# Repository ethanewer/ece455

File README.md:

# ECE 455 proton magnetometer

One proton precession magnetometer design: a polarization board, a signal-processing and control board with a Raspberry Pi Pico 2 and an ADS1256 ADC, an off-board two-stage amplifier, the sensing and polarizing coils, and the Pico firmware. [`docs/design.md`](docs/design.md) describes how they fit together and lists open issues.

## Layout

Design files, one folder per type:

| Folder | Contents | Edit with |
|---|---|---|
| [`kicad/`](kicad/) | Polarization board and signal-processing & control board: schematics, PCBs, Gerbers, BOM | KiCad 10 |
| [`ltspice/`](ltspice/) | `AmplificationSim.asc`: coil, tuning tank, and the off-board amplifier | LTspice |
| [`firmware/`](firmware/) | Pico 2 ADS1256 capture and frequency firmware, and its serial plotter | Pico SDK 2.3.1 |
| [`spreadsheets/`](spreadsheets/) | `CoilDesign.xlsx`: coil windings and polarizing field; `TuningCapacitors.xlsx`: measured coil inductances and LC tuning | Excel |
| [`3d_models/`](3d_models/) | Sensing coil V1 and polarizing coil V2 forms: SolidWorks parts and sliced print files | SolidWorks, Bambu Studio |

Everything else:

- [`util/`](util/) reads those files and holds the simulation, breadboard layout, firmware host harness, and tests.
- [`docs/`](docs/) has the design description, the verification plan, generated simulation and breadboard reports, datasheets, and references.
- `local/` is for uncommitted output.

## Setup

```sh
python3 -m venv .venv
. .venv/bin/activate
pip install -e '.[test,bench]'
brew install ngspice        # or: sudo apt-get install ngspice
```

`make firmware` and `make test` compile the firmware on the host with `$CC`, or clang or gcc. Building and flashing the Pico needs the Pico SDK and Arm toolchain; see [`firmware/README.md`](firmware/README.md).

## Commands

```sh
make test         # all tests: board/schematic/BOM/firmware consistency, coil forms, LTspice translation, breadboard, estimator
make firmware     # only the firmware estimator tests
make sim          # simulate ltspice/AmplificationSim.asc and regenerate docs/simulation/
make breadboard   # check the breadboard layout and regenerate docs/breadboard/
make verify       # test, sim, and breadboard
make flash        # build the Pico firmware and flash it over USB
make plot         # plot captures from the Pico (sets up .venv on first use)
```

## Status

Both PCBs match their schematics, and the firmware's SPI pins match the ADS1256 header on J3. The amplifier exists only as an LTspice drawing and a breadboard layout; no op amp has been chosen. From the coil workbook and print files, the coils as built should give a best-case FID of about 2 µV, a fifth of the drawing's 10 µV. The coil forms are sized for the sensing coils to sit inside the polarizing coil, where its turn-off would induce on the order of 100 V in them, beyond what the damping switch and amplifier input are rated for. The firmware now polarizes and captures on a button press but does not drive the damping switch. Nothing here has been measured on hardware; see [`docs/verification-plan.md`](docs/verification-plan.md).

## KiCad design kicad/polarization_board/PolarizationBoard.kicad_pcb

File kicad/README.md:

# KiCad projects

Two KiCad 10 projects. Open the `.kicad_pro` file in KiCad.

| Folder | Board | Files |
|---|---|---|
| `polarization_board/` | Battery, fuse, 12 V regulator, TC4420 gate driver, and the NMOS switch and TVS for the polarizing coil | `PolarizationBoard.kicad_{pro,sch,pcb}`, `gerbers/` |
| `signal_control_board/` | Coil input, switched tuning bank, damping switch, amplifier connectors J5/J6, 5 V buck converter, 2.5 V bias, ADC input network, sockets for the ADS1256 module, and the Pico 2 | `SignalProcessing&ControlBoard.kicad_{pro,sch,pcb}`, sub-sheets `SignalProcessing.kicad_sch` and `MCU.kicad_sch`, `gerbers/`, and the BOM export `SignalProcessing&ControlBoard.csv` |

Keep the file names: the root schematic refers to its sub-sheets by name. After changing a board, re-export its Gerbers into `gerbers/` (and the signal board's BOM CSV), then run `make test`. The tests read these files directly with `util/kicad.py`. They check each board's nets against its schematic and compare the boards with the firmware, the LTspice drawing, and the breadboard layout. They do not replace KiCad ERC and DRC, which need KiCad itself. `.kicad_prl` files and `.history/` folders are local editor state and are not committed.

[`../docs/design.md`](../docs/design.md) describes both boards.

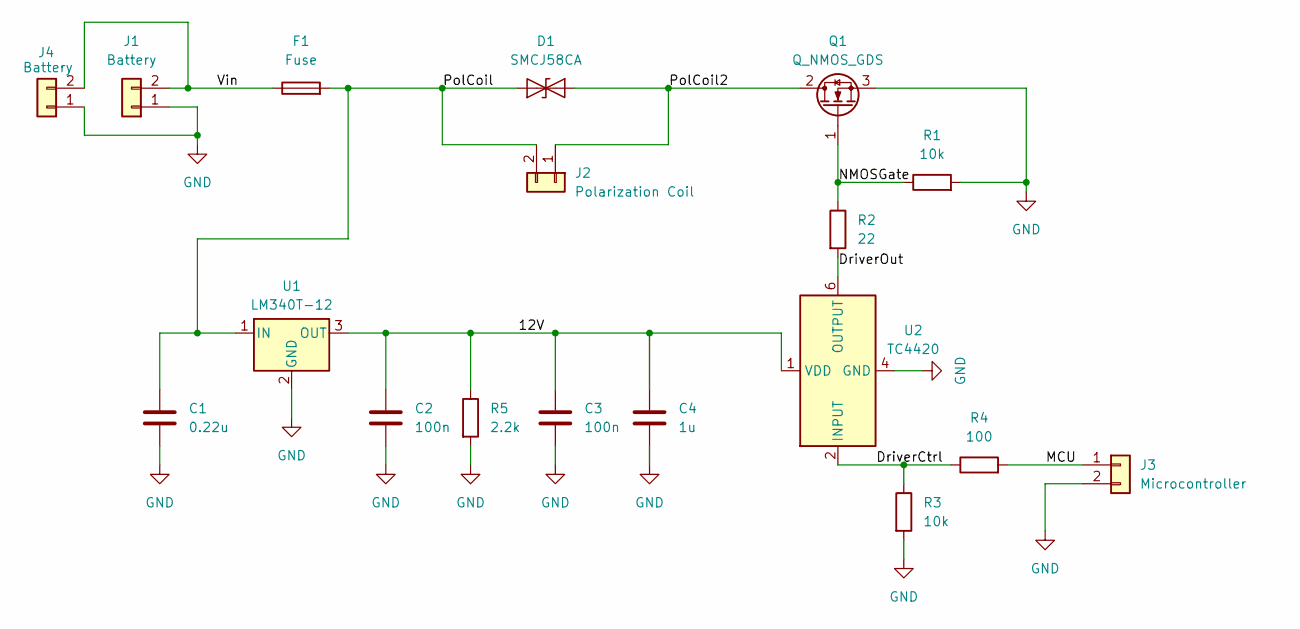
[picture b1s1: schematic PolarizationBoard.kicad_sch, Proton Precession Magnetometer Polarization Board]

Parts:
C1: 0.22u; C_1206_3216Metric_Pad1.33x1.80mm_HandSolder; Manufacturing Part Numb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 GRM319R71H224KA01D
C2, C3: 100n; C_1206_3216Metric_Pad1.33x1.80mm_HandSolder; Manufacturing Part Numb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 12065C104K4T2A
C4: 1u; C_1206_3216Metric_Pad1.33x1.80mm_HandSolder; Manufacturing Part Numb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 GRM31CR71H105KA61L
D1: SMCJ58CA; D_SMC_Handsoldering; Manufacturing Part Numb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 SMCJ58CA
F1: Fuse; Fuseholder_Cylinder-5x20mm_Schurter_0031_8201_Horizontal_Op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; Manufacturing Part Numb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 0031.8201
J1, J4: Battery; TerminalBlock_Phoenix_MKDS-1,5-2_1x02_P5.00mm_Horizontal; Manufacturing Part Numb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 1715721
J2: Polarization Coil; TerminalBlock_Phoenix_MKDS-1,5-2_1x02_P5.00mm_Horizontal; Manufacturing Part Numb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 1715721
J3: Microcontroller; TerminalBlock_Phoenix_MKDS-1,5-2_1x02_P5.00mm_Horizontal; Manufacturing Part Numb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 1715721
Q1: Q_NMOS_GDS; TO-220-3_Vertical; Manufacturing Part Numb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 IRFB4227PBF
R1, R3: 10k; R_1206_3216Metric_Pad1.30x1.75mm_HandSolder; Manufacturing Part Numb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 RMCF1206FT10K0
R2: 22; R_1206_3216Metric_Pad1.30x1.75mm_HandSolder; Manufacturing Part Numb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 RMCF1206JT22R0
R4: 100; R_1206_3216Metric_Pad1.30x1.75mm_HandSolder; Manufacturing Part Numb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 RMCF1206FT100R
R5: 2.2k; R_1206_3216Metric_Pad1.30x1.75mm_HandSolder; Manufacturing Part Numb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 RMCF1206FT2K20
U1: LM340T-12; TO-220-3_Vertical; Manufacturing Part Numb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 LM340T-12/NOPB
U2: TC4420; SOIC-8_3.9x4.9mm_P1.27mm; Manufacturing Part Numb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 TC4420VOA713

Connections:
/12V: C2.1, C3.1, C4.1, R5.1, U1.3 (OUT), U2.1 (VDD), U2.8 (VDD)
/DriverCtrl: R3.1, R4.1, U2.2 (INPUT)
/DriverOut: R2.2, U2.6 (OUTPUT), U2.7 (OUTPUT)
/MCU: J3.1, R4.2
/NMOSGate: Q1.1 (G), R1.1, R2.1
/PolCoil: C1.1, D1.1 (A1), F1.2, J2.2, U1.1 (IN)
/PolCoil2: D1.2 (A2), J2.1, Q1.2 (D)
/Vin: F1.1, J1.2, J4.2
GND: C1.2, C2.2, C3.2, C4.2, J1.1, J3.2, J4.1, Q1.3 (S), R1.2, R3.2, R5.2, U1.2 (GND), U2.4 (GND), U2.5 (GND)

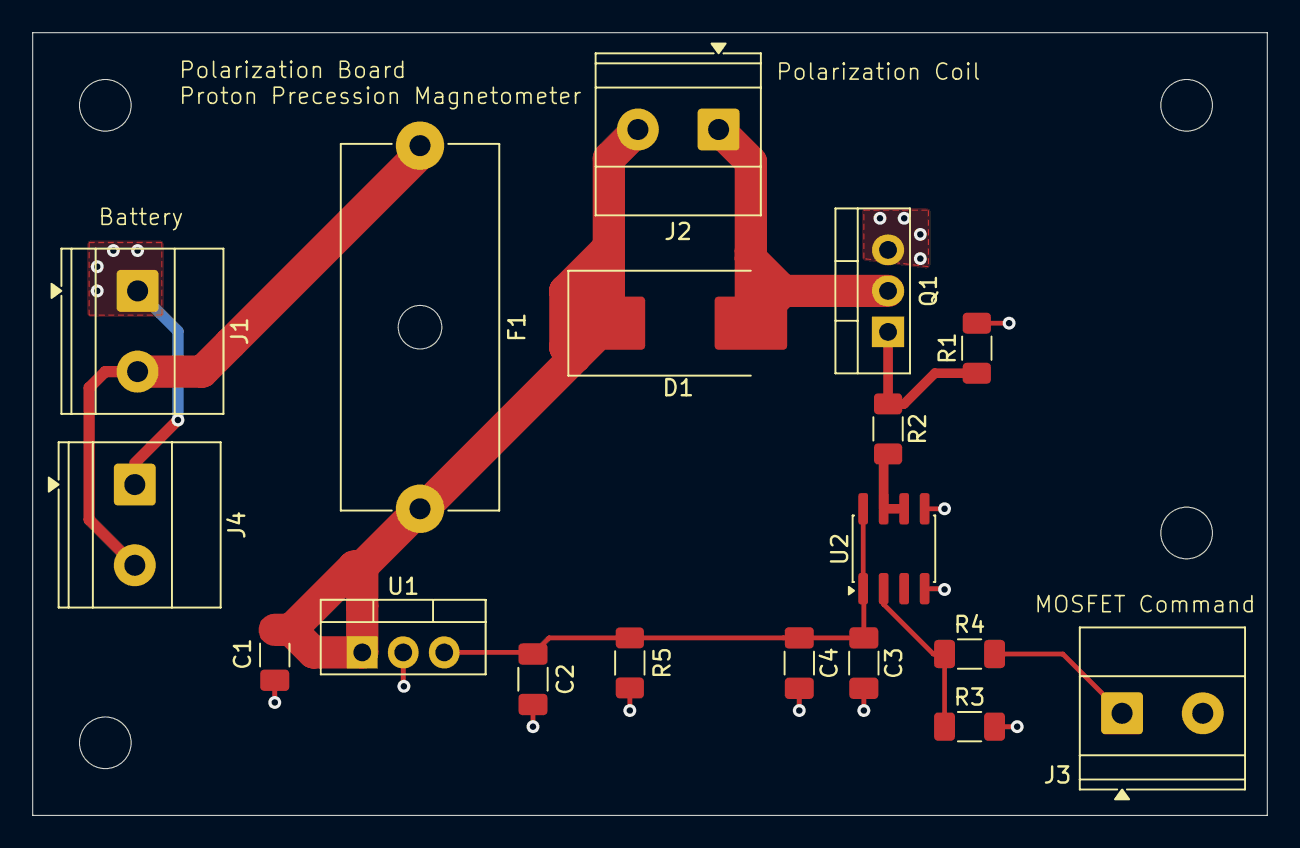
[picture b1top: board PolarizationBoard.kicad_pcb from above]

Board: 2 copper layers, 76.5 x 48.5 mm, 22 parts (0 on the bottom side), 9 nets.

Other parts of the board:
H1, H2, H3, H4: MountingHole_3.2mm_M3

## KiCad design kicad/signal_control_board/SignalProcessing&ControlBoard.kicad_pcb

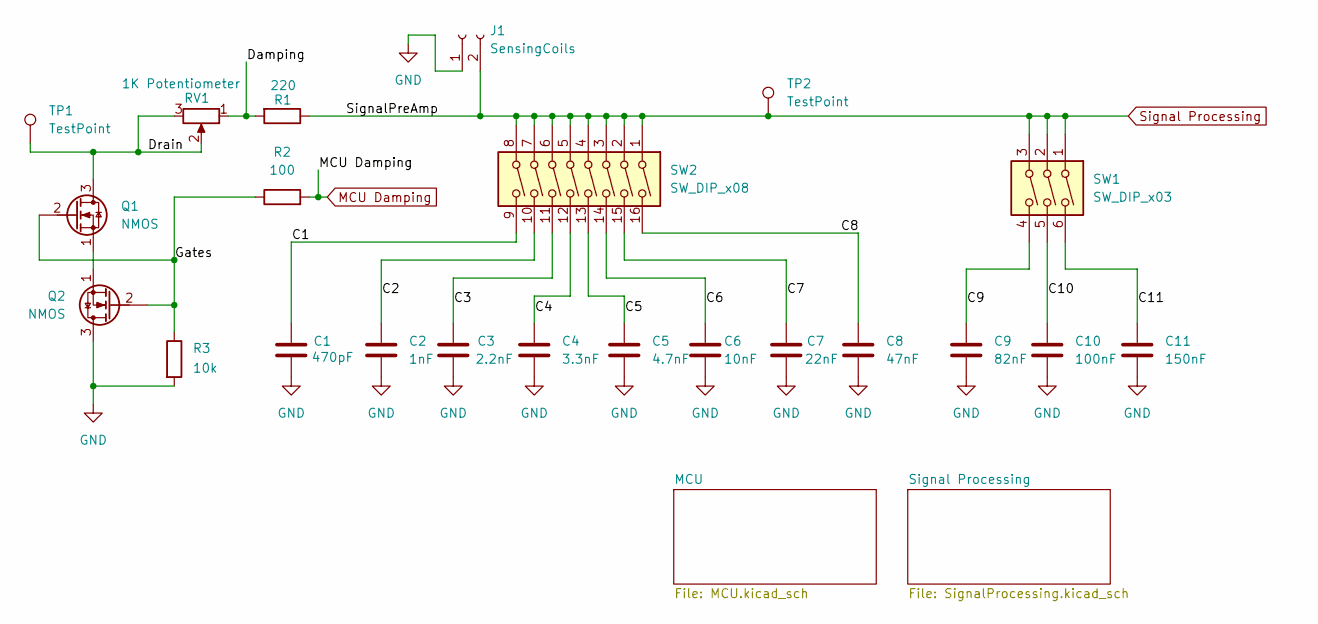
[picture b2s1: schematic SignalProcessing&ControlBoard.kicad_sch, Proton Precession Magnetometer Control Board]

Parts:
C1: 470pF; C_1206_3216Metric_Pad1.33x1.80mm_HandSolder
C2: 1nF; C_1206_3216Metric_Pad1.33x1.80mm_HandSolder
C3: 2.2nF; C_1210_3225Metric_Pad1.33x2.70mm_HandSolder
C4: 3.3nF; C_1206_3216Metric_Pad1.33x1.80mm_HandSolder
C5: 4.7nF; C_1206_3216Metric_Pad1.33x1.80mm_HandSolder
C6: 10nF; C_1206_3216Metric_Pad1.33x1.80mm_HandSolder
C7: 22nF; C_Rect_L13.0mm_W6.0mm_P10.00mm_FKS3_FKP3_MKS4
C8: 47nF; C_Rect_L18.0mm_W6.0mm_P15.00mm_FKS3_FKP3
C9: 82nF; C_Rect_L26.5mm_W6.0mm_P22.50mm_MKS4
C10: 100nF; C_Rect_L18.0mm_W9.0mm_P15.00mm_FKS3_FKP3
C11: 150nF; C_Rect_L18.0mm_W11.0mm_P15.00mm_FKS3_FKP3
J1: SensingCoils; TerminalBlock_Phoenix_MKDS-1,5-2-5.08_1x02_P5.08mm_Horizont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
Q1, Q2: NMOS; TO-92_Inline
R1: 220; R_1206_3216Metric_Pad1.30x1.75mm_HandSolder
R2: 100; R_1206_3216Metric_Pad1.30x1.75mm_HandSolder
R3: 10k; R_1206_3216Metric_Pad1.30x1.75mm_HandSolder
RV1: 1K Potentiometer; Potentiometer_Bourns_3296W_Vertical
SW1: SW_DIP_x03; SW_DIP_SPSTx03_Slide_9.78x9.8mm_W7.62mm_P2.54mm
SW2: SW_DIP_x08; SW_DIP_SPSTx08_Slide_9.78x22.5mm_W7.62mm_P2.54mm
TP1, TP2: TestPoint; TestPoint_Keystone_5000-5004_Miniature

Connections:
/C1: C1.1, SW2.9
/C2: C2.1, SW2.10
/C3: C3.1, SW2.11
/C4: C4.1, SW2.12
/C5: C5.1, SW2.13
/C6: C6.1, SW2.14
/C7: C7.1, SW2.15
/C8: C8.1, SW2.16
/C9: C9.1, SW1.4
/C10: C10.1, SW1.5
/C11: C11.1, SW1.6
/Damping: R1.2, RV1.1
/Drain: Q1.3 (D), RV1.2, RV1.3, TP1.1 (1_1)
/Gates: Q1.2 (G), Q2.2 (G), R2.1, R3.1
GND: C1.2, C2.2, C3.2, C4.2, C5.2, C6.2, C7.2, C8.2, C9.2, C10.2, C11.2, J1.1, Q2.3 (D), R3.2; also elsewhere on the board
MCU Damping: R2.2; also elsewhere on the board
unnamed: Q1.1 (S), Q2.1 (S)
Signal Processing: J1.2, R1.1, SW1.1, SW1.2, SW1.3, SW2.1, SW2.2, SW2.3, SW2.4, SW2.5, SW2.6, SW2.7, SW2.8, TP2.1 (1_1); also elsewhere on the board

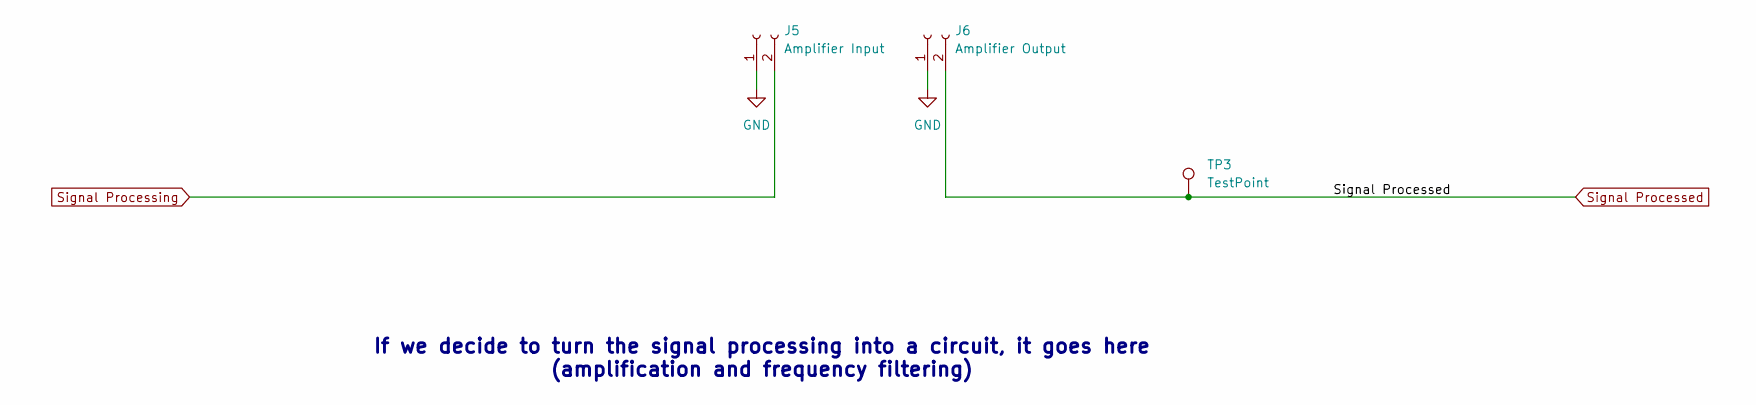
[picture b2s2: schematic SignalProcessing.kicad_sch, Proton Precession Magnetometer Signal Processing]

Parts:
J5: Amplifier Input; TerminalBlock_Phoenix_MKDS-1,5-2-5.08_1x02_P5.08mm_Horizont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
J6: Amplifier Output; TerminalBlock_Phoenix_MKDS-1,5-2-5.08_1x02_P5.08mm_Horizont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
TP3: TestPoint; TestPoint_Keystone_5000-5004_Miniature

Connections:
GND: J5.1, J6.1; also elsewhere on the board
Signal Processed: J6.2, TP3.1 (1_1); also elsewhere on the board
Signal Processing: J5.2; also elsewhere on the board

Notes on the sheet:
If we decide to turn the signal processing into a circuit, it goes here (amplification and frequency filtering)

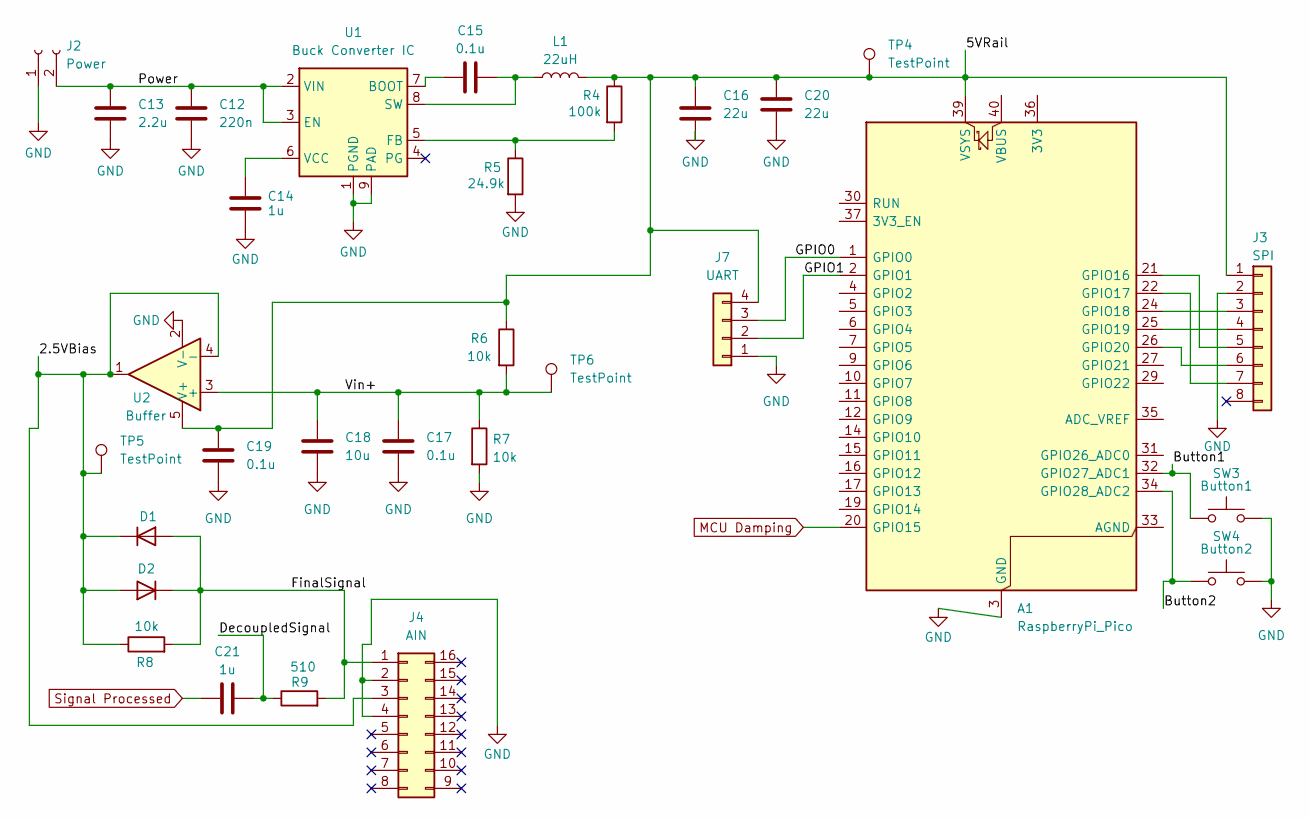
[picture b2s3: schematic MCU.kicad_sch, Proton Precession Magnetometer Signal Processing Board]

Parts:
A1: RaspberryPi_Pico; RaspberryPi_Pico_Common_Unspecified
C12: 220n; C_1206_3216Metric_Pad1.33x1.80mm_HandSolder
C13: 2.2u; C_1206_3216Metric_Pad1.33x1.80mm_HandSolder
C14, C21: 1u; C_1206_3216Metric_Pad1.33x1.80mm_HandSolder
C15, C17, C19: 0.1u; C_1206_3216Metric_Pad1.33x1.80mm_HandSolder
C16, C20: 22u; C_1206_3216Metric_Pad1.33x1.80mm_HandSolder
C18: 10u; C_1206_3216Metric_Pad1.33x1.80mm_HandSolder
D1, D2: D; D_SOD-123
J2: Power; TerminalBlock_Phoenix_MKDS-1,5-2-5.08_1x02_P5.08mm_Horizont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
J3: SPI; PinSocket_1x08_P2.54mm_Vertical
J4: AIN; PinSocket_2x08_P2.54mm_Vertical
J7: UART; PinSocket_1x04_P2.54mm_Vertical
L1: 22uH; L_Wurth_7447714220_WE-PD_1050
R4: 100k; R_1206_3216Metric_Pad1.30x1.75mm_HandSolder
R5: 24.9k; R_1206_3216Metric_Pad1.30x1.75mm_HandSolder
R6, R7, R8: 10k; R_1206_3216Metric_Pad1.30x1.75mm_HandSolder
R9: 510; R_1206_3216Metric_Pad1.30x1.75mm_HandSolder
SW3: Button1; SW_PUSH_6mm_H9.5mm
SW4: Button2; SW_PUSH_6mm_H9.5mm
TP4, TP5, TP6: TestPoint; TestPoint_Keystone_5000-5004_Miniature
U1: Buck Converter IC; Texas_HTSOP-8-1EP_3.9x4.9mm_P1.27mm_EP2.95x4.9mm_Mask2.4x3.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
U2: Buffer; SOT-23-5

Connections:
/MCU/2.5VBias: D1.1 (K), D2.2 (A), J4.3, R8.1, TP5.1 (1_1), U2.1, U2.4 (-)
/MCU/5VRail: A1.39 (VSYS), C16.2, C19.1, C20.2, J3.1, J7.4, L1.2, R4.1, R6.1, TP4.1 (1_1), U2.5 (V+)
/MCU/Button1: A1.32 (GPIO27_ADC1), SW3.1
/MCU/Button2: A1.34 (GPIO28_ADC2), SW4.1
/MCU/DecoupledSignal: C21.2, R9.1
/MCU/FinalSignal: D1.2 (A), D2.1 (K), J4.1, R8.2, R9.2
/MCU/GPIO0: A1.1 (GPIO0), J7.3
/MCU/GPIO1: A1.2 (GPIO1), J7.2
/MCU/Power: C12.1, C13.1, J2.2, U1.2 (VIN), U1.3 (EN)
/MCU/Vin+: C17.1, C18.1, R6.2, R7.1, TP6.1 (1_1), U2.3 (+)
GND: A1.3 (GND), A1.8 (GND), A1.13 (GND), A1.18 (GND), A1.23 (GND), A1.28 (GND), A1.38 (GND), C12.2, C13.2, C14.2, C16.1, C17.2, C18.2, C19.2, C20.1, J2.1, J3.2, J4.2, J4.4, J7.1, R5.2, R7.2, SW3.2, SW4.2, U1.1 (PGND), U1.9 (PAD), U2.2 (V-); also elsewhere on the board
MCU Damping: A1.20 (GPIO15); also elsewhere on the board
unnamed: A1.21 (GPIO16), J3.5
unnamed: A1.22 (GPIO17), J3.7
unnamed: A1.24 (GPIO18), J3.3
unnamed: A1.25 (GPIO19), J3.4
unnamed: A1.26 (GPIO20), J3.6
unnamed: C15.1, U1.7 (BOOT)
unnamed: R4.2, R5.1, U1.5 (FB)
unnamed: C15.2, L1.1, U1.8 (SW)
unnamed: C14.1, U1.6 (VCC)
Signal Processed: C21.1; also elsewhere on the board

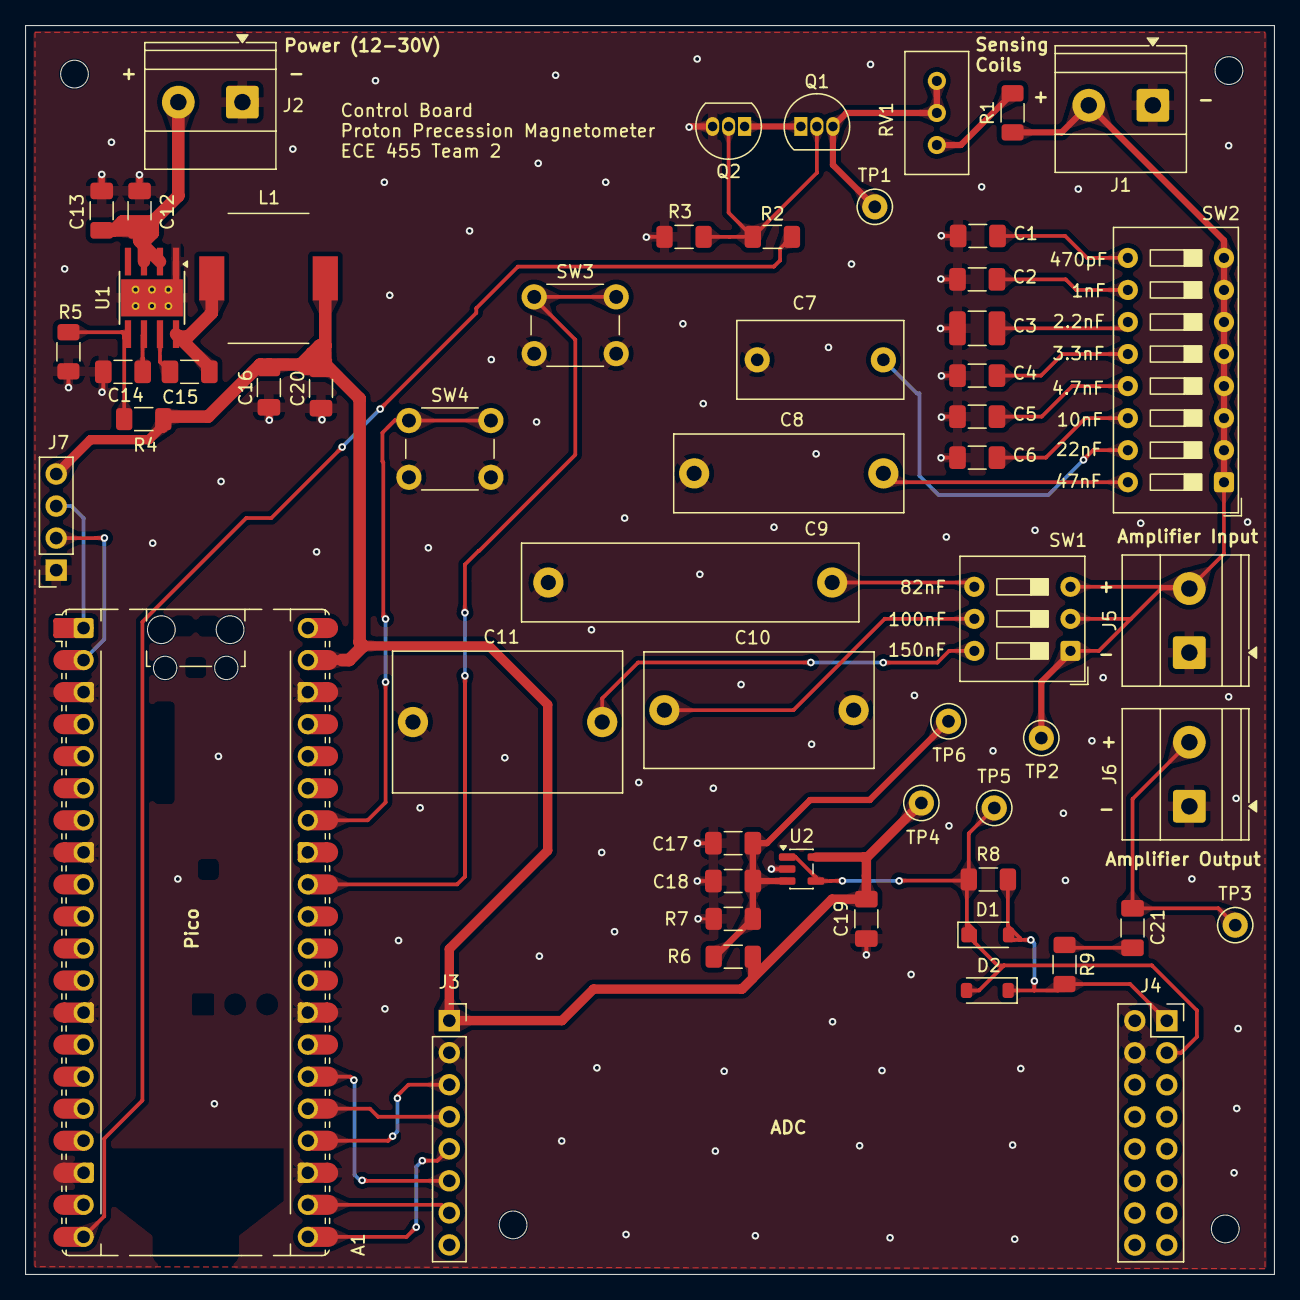
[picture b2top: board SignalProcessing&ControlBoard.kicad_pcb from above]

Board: 2 copper layers, 99.0 x 99.0 mm, 60 parts (0 on the bottom side), 38 nets.

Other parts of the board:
Hole1, Hole2, Hole3, Hole4: MountingHole_2.2mm_M2

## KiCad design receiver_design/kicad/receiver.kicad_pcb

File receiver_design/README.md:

# Active receiver design

The receiver is a purchased AD8421 instrumentation-amplifier module followed by a two-section RC anti-aliasing filter. It sits between the external sensor (J1) and the already purchased HiLetgo ADS1256 module, which is controlled by the already purchased Seeed XIAO RP2350. Everything to buy is listed, with Amazon links and prices, in [`amazon_purchases.json`](../amazon_purchases.json) at the repository root: $48.95 of a $50 budget for the required items, or $86.62 with the recommended spare module and clip-on ferrites.

## Requirements

`requirements.py` defines the requirements, and **`make verify` fails if any of them is missed**. `verify.py` simulates the deck at ten corners and exits with an error listing each failure:

- nominal;
- 0 °C and 50 °C;
- 4.75 V USB;
- batteries at 6.0 V (end of life) and 9.6 V (fresh);
- filter capacitors −10% with R1 −5%, and +10% with R1 +5%;
- two stacked corners. The first is 50 °C, 4.75 V USB, 6.0 V batteries, BIAS trimmed to 2.75 V, capacitors −10%, and R1 −5%. The second is 50 °C, BIAS 2.25 V, capacitors +10%, and R1 +5%.

| Requirement | Limit | How it is checked |
|---|---|---|
| Input impedance at J1 | \|Z_in\| ≥ 1 MΩ everywhere in 1.5–2.5 kHz | ngspice AC, V(J1)/I(source) |
| Noise | ≤ 5 nV/√Hz everywhere in 1.6–2.2 kHz | ngspice `.noise` with the untuned coil pair at J1, referred to the coil EMF, plus the ADS1256's 10.3 µV RMS referred through the minimum in-band gain |
| Interference | No clipping for a **10 mV peak tone at 50–400 Hz** or a **2 mV peak tone at 8–50 kHz** at J1 | DC headroom divided by gain from J1 at the AD8421 input range, the AD8421 output swing, and the ADS1256 AIN0 range |
| Anti-aliasing | Gain from J1 to AIN0 within 2.2 kHz of 1.92 MHz at least **90 dB** below the minimum in-band gain | ngspice AC across 1.9178–1.9222 MHz |

The noise limit comes from the frequency Cramér–Rao bound. At 5 nV/√Hz it is about 0.24 nT for the pessimistic 0.41 µV FID, a 4× margin under the 1 nT target. The interference limits cover mains and its harmonics, plus switching and audio-band pickup.

The ADS1256 is a delta-sigma converter. Its modulator samples at 1.92 MHz, and its digital filter rejects anything that would fold into 1.6–2.2 kHz by at least 110 dB at 30 kSPS. The exception is the band around 1.92 MHz itself, where the filter's response repeats. Only an analog filter can reject that band, which is why the anti-aliasing requirement exists.

There is no minimum gain requirement. The gain only has to make the ADC's own noise small, and the noise requirement already includes it.

## Simulated performance

These are ngspice values from `spice/receiver.cir` with a datasheet-based AD8421 model (see `analysis/README.md` and the `make verify` table), not measurements.

| Quantity | Nominal | Worst of ten corners |
|---|---|---|
| Gain J1 → AIN0, 1.6–2.2 kHz | 83.4–87.0 V/V | ≥ 77.9 V/V |
| \|Z_in\|, 1.5–2.5 kHz | 4.25–7.08 MΩ | ≥ 4.21 MΩ |
| Input noise with the untuned coil, including the ADC | 3.89 nV/√Hz | ≤ 4.06 nV/√Hz |
| Largest tone without clipping, 50–400 Hz | 27.2 mV (AIN0 range) | 15.7 mV |
| Largest tone without clipping, 8–50 kHz | 49.0 mV (AD8421 output) | 15.7 mV |
| Alias rejection near 1.92 MHz | 98.2 dB | ≥ 96.5 dB |
| Frequency CRB, untuned coil | 0.021 nT (3.59 µV FID), 0.188 nT (0.41 µV FID) | — |
| Input noise, 30 kΩ tuned-sensor fixture | 23.4 nV/√Hz, 0.4 dB noise figure | — |
| Low-pass −3 dB corner | 4.57 kHz | — |
| DC at AD8421 OUT / AIN0 | 2.50 V / 2.39 V | — |

The ADC's converter noise referred to J1 is 1.0 nV/√Hz. The amplifier alone (input shorted) is 3.6 nV/√Hz: the AD8421's 3.2 nV/√Hz maximum, R1's 1.3 nV/√Hz, and its 60 nV/√Hz output noise divided by the gain.

With the external tuning capacitor fitted, the receiver adds little: the 30 kΩ fixture result is 0.4 dB above the source's own thermal noise. Referred to the coil EMF that is about 1.35 nV/√Hz, against 3.89 nV/√Hz untuned, so tuning the coil is the largest remaining noise improvement.

A more expensive amplifier would not help. The AD8429 (1 nV/√Hz, but 1.5 pA/√Hz current noise) simulates at 3.86 nV/√Hz with the untuned coil and 50 nV/√Hz with the 30 kΩ fixture. The coil's roughly 2 kΩ reactance, and the tuned tank's 30 kΩ, turn its current noise into voltage noise. The ADC already contributes only 1.0 nV/√Hz, so a better converter would not help either.

The worst interference corner has 6.0 V batteries, BIAS at 2.75 V, and the highest gain. There the AD8421 output reaches its +VS − 1.6 V swing limit first.

## Circuit

Reference designators match `spice/receiver.cir`, `bom.csv`, and the construction schematic.

1. **Input clamps.** Q1 and Q2 are 2N3904s connected as diodes, collector tied to base. They clamp J1 to about ±0.65 V with negligible leakage. The AD8421 also tolerates 40 V from the opposite rail, but the clamps limit what reaches it during the polarizer turnoff.
2. **AD8421 module (MOD2), gain 100.**
   - The module's input jumper ties −IN to GND, so J1 drives +IN single-ended.
   - R1 (100 Ω) fits the module's GAIN footprint: G = 1 + 9.9 kΩ/R1 = 100.
   - The module's BIAS trimmer and on-board buffer drive REF. With J1 shorted, trim OUT to 2.50 V, the middle of AIN0's range.
   - The module's input RFI network must be removed (see `assembly.md`). The datasheet example (1 nF common mode, 10 nF differential) would load J1 to a few kilohms and detune the coil. A test in `tests/test_eda.py` shows that it fails the |Z_in| requirement.
   - Two 9 V batteries (BT1, BT2) through snap leads (W2, W3) give ±9 V. Their midpoint is the system ground.
3. **Cable.** W1, an SMA-to-Dupont lead, carries OUT from the module's SMA jack to the breadboard.
4. **Anti-aliasing filter.** R2 (1 kΩ) with C1 (22 nF), then R3 (10 kΩ) with C2 (2.2 nF), both poles near 7.2 kHz.
   - The second section has ten times the impedance of the first, so the sections barely load each other.
   - Response: −0.8 dB at 2.2 kHz, −14 dB at the 15 kHz Nyquist frequency, and about −96 dB at 1.92 MHz.
   - The 11 kΩ in series also limits fault current into AIN0 to under 1 mA, well inside the ADS1256's 10 mA input-current rating. External clamp diodes are therefore not fitted.
5. **ADC.** AIN0 takes the filter output and AIN1 is wired to GND.

## ADC configuration and SPI

Configure the ADS1256 for AIN0 − AIN1, input buffer **off**, **PGA 1** (±5 V full scale), and 30 kSPS. With the buffer off, AIN0 may span AGND − 0.1 V to AVDD + 0.1 V, so AIN1 can sit at GND and AIN0 at 2.4 V. The converter noise at this setting is 10.3 µV RMS (TI Table 4), the same as with the buffer on. The model includes the unbuffered input's effective impedance (TI Table 10, 260 kΩ and 220 kΩ at PGA 1), which costs about 8% of the gain. Leave AIN2–AIN7 unconnected.

The SPI connects **directly** to the XIAO. The ADS1256 datasheet specifies SCLK, DIN, CS, and SYNC/PDWN as inputs accepting up to 5.25 V. DOUT and DRDY swing only to DVDD, which is at most 3.6 V. Before connecting, measure the powered module's DRDY high level; expect about 3.3 V.

| Function | XIAO pin | RP2350 GPIO | Module pin |
|---|---|---:|---|
| ADS1256 DRDY | D2 | GPIO28 | DRDY (input to XIAO) |
| ADS1256 CS | D3 | GPIO5 | CS |
| ADS1256 SYNC/PDWN | D4 | GPIO6 | PDWN |
| SPI0 SCLK | D8 | GPIO2 | SCLK |
| SPI0 MISO | D9 | GPIO4 | DOUT |
| SPI0 MOSI | D10 | GPIO3 | DIN |
| 5 V / GND | VBUS / GND | — | 5V / GND |

Firmware must do the following:

1. Drive CS and SYNC/PDWN high.
2. Wait for DRDY.
3. Configure the ADC.
4. For each measurement, ignore conversions during the blank.
5. Pulse SYNC/PDWN low briefly (under 20 DRDY periods) and wait for DRDY before recording.

At 30 kSPS the SPI needs at least 720 kbit/s for 24-bit data, plus command overhead.

J2–J5 give **logical signal names**, not the purchased boards' physical header order. Verify the ADS1256 module's header order and the AD8421 module's jumpers against the boards in hand before wiring. Check each kit transistor's lead order against its marking and datasheet before soldering. KiCad TO-92 symbols number pins 1/2/3 as E/B/C.

## Protection limits

Q1/Q2 take the polarizer turnoff current at J1, limited only by the external sensor's impedance. The 2N3904 is rated 200 mA collector current. The SPICE models do not prove surge survival, and the AD8421 model does not clip or recover from overload. Measure the actual polarizer turnoff voltage and current at the sensor output before connecting it, then measure the AD8421's recovery after the blank.

## Files and status

- `../amazon_purchases.json` lists everything to buy, with links, prices, and the budget. `verify.py` checks that the BOM uses every required item, that the required total fits the budget, and that the recommended extras (spare module, ferrites) have valid links and totals.
- `requirements.py` defines the requirements, the corner set, and the checker used by `verify.py`, the tests, and the analysis report.
- `spice/receiver.cir` is the active ngspice model. It contains the AD8421 behavioral model, which uses datasheet values (Rev. 0) for input impedance, noise, gain, and bandwidth. It omits the module's BIAS/REF path noise, ADC converter noise, the digital filter, SPI timing, firmware blanking, and the external sensor's LC response.
- `analyze.py` generates the committed `analysis/` CSV, PNG, and Markdown artifacts, including |Z_in|, interference tolerance, alias rejection, and the noise/CRB table.
- `schematic.py` draws the construction schematic used by `make export` and `docs/`.
- `breadboard.py` holds the fixed placement on a standard 830-point breadboard, laid out as the board was built, and draws it with the AD8421 module, batteries, cable, ADS1256 module, and XIAO (`docs/receiver-breadboard.png`). It includes a 1000:1 divider so a function generator can stand in for the coil. `make export` checks the receiver against `spice/receiver.cir` and the XIAO-to-ADS1256 wires against `kicad/receiver.net`, then draws the board and lists every hole.
- `bom.csv` lists every fitted and purchased part. Lab parts come from `new_allowed_components.json`.
- `assembly.md` covers module preparation, wiring, and the bring-up sequence.
- `kicad/generate.py` emits the text connectivity netlist `kicad/receiver.net`. `verify.py` checks that it, the SPICE deck, and the BOM describe the same parts and pins. There is no graphical KiCad schematic or PCB, and `make pcb` intentionally fails.

Data sources:

- [Analog Devices AD8421 datasheet](https://www.analog.com/media/en/technical-documentation/data-sheets/ad8421.pdf): noise, input impedance, input and output ranges, gain equation, bandwidth, and the RFI filter example.
- [TI ADS1256 datasheet](https://www.ti.com/lit/ds/symlink/ads1256.pdf): absolute maximum ratings, unbuffered input range and impedance, digital-filter response, digital I/O levels, and Table 4 input-referred noise.
- [onsemi 2N3904 datasheet](https://www.onsemi.com/pdf/datasheet/2n3904-d.pdf): pinout and limits.

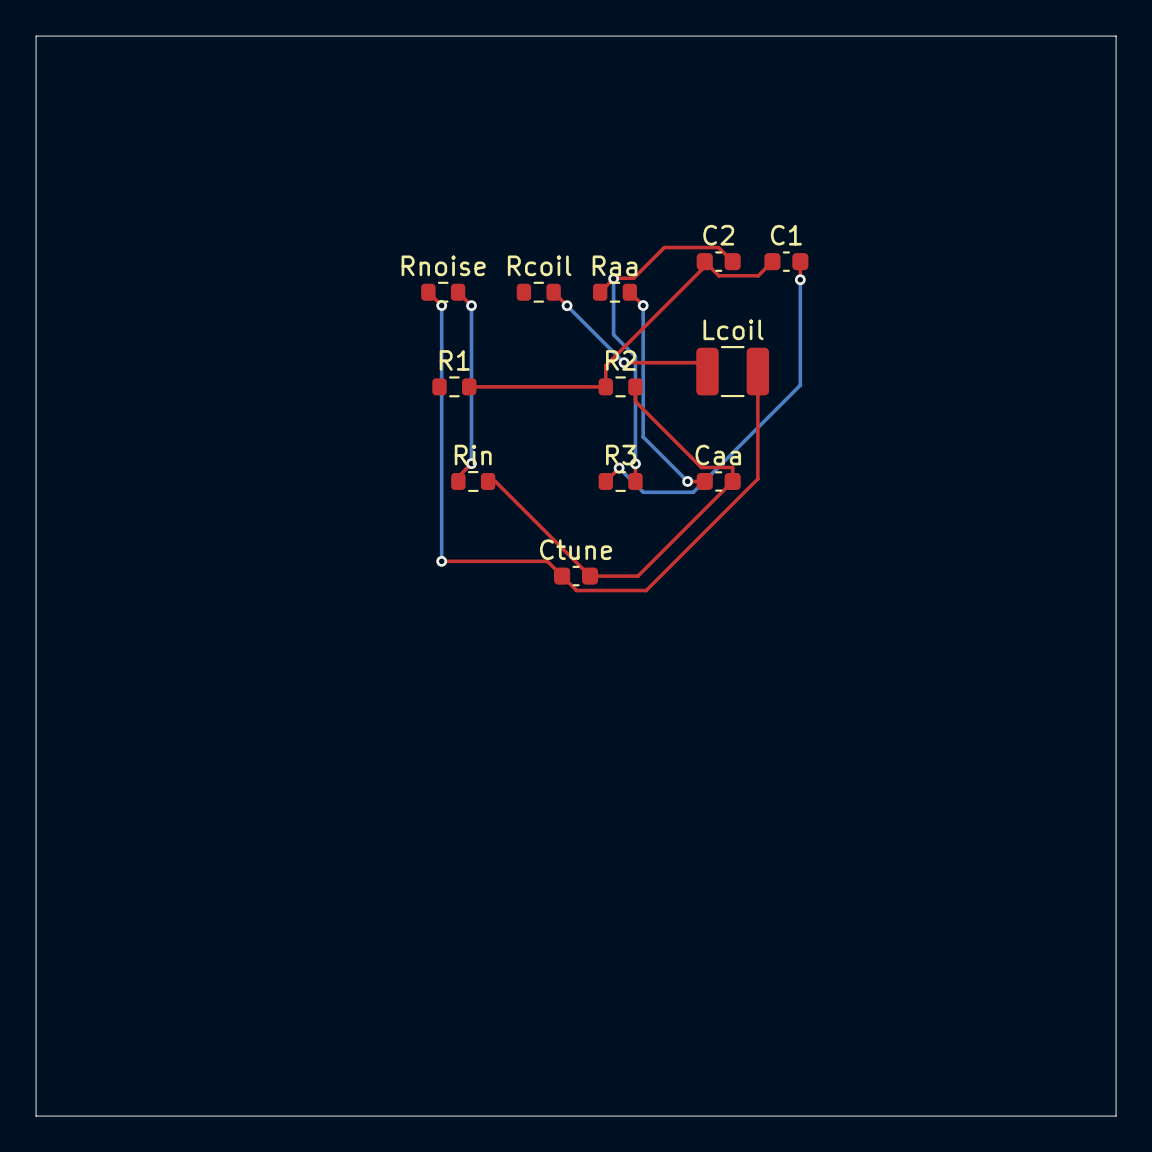
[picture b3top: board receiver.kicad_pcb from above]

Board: 2 copper layers, 60.0 x 60.0 mm, 12 parts (0 on the bottom side), 8 nets.

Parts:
C1, C2: 22n; C_0603_1608Metric
Caa: 22n; C_0603_1608Metric
Ctune: 2.540621742085708e-07; C_0603_1608Metric
Lcoil: 0.022; L_1210_3225Metric
R1: 1700.94; R_0603_1608Metric
R2: 1130.63; R_0603_1608Metric
R3: 17009.4; R_0603_1608Metric
Raa: 1k; R_0603_1608Metric
Rcoil: 14.0; R_0603_1608Metric
Rin: 1.657e+06; R_0603_1608Metric
Rnoise: 118.3; R_0603_1608Metric

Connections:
GND: Caa.2, Ctune.2, R2.2, Rin.2
nA: C1.1, C2.1, R1.2, R2.1
naa: Caa.1, Raa.2
nc: Lcoil.1, Rcoil.2
nin: Ctune.1, Lcoil.2, Rnoise.1
ninv: C1.2, R3.1
np: Rin.1, Rnoise.2
outbp: C2.2, R3.2, Raa.1
